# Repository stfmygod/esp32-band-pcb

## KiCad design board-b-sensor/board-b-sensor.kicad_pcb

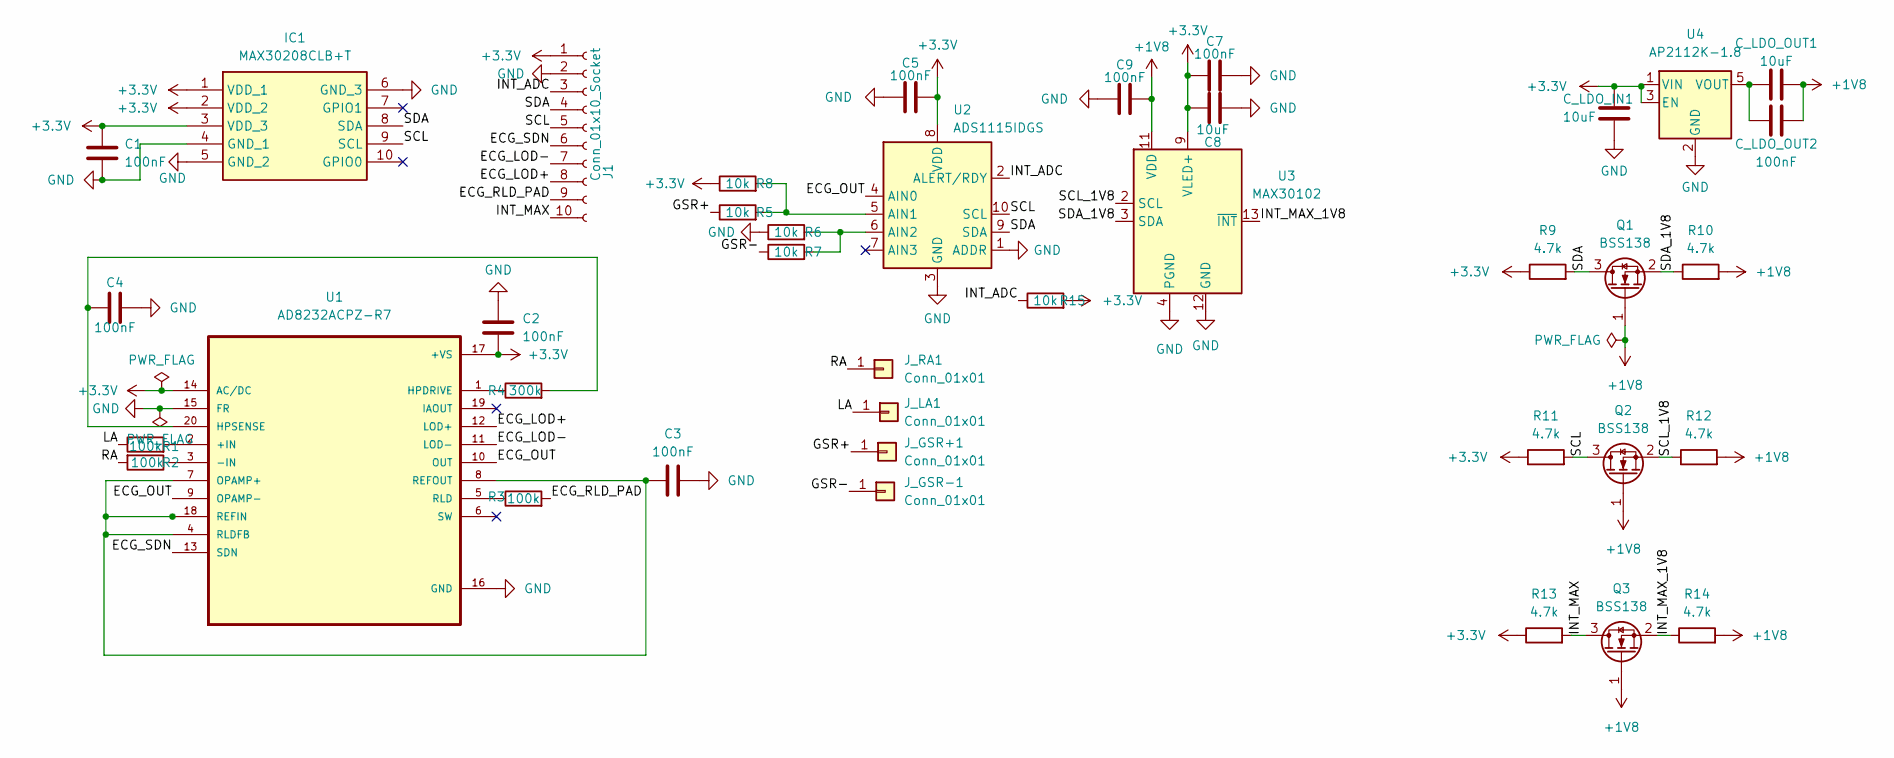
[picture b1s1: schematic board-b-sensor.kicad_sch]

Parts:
C1, C2, C3, C4, C5, C7, C9: 100nF; C_0402_1005Metric
C8: 10uF; C_0805_2012Metric
C_LDO_IN1: 10uF; C_0805_2012Metric
C_LDO_OUT1: 10uF; C_0805_2012Metric
C_LDO_OUT2: 100nF; C_0402_1005Metric
IC1: MAX30208CLB+T; MAX30208CLBT; Manufacturer_Part_Number MAX30208CLB+T; Mouser Part Number 700-MAX30208CLB+T
J1: Conn_01x10_Socket; FPC-SMD_10P-P0.50_XUNPU_FPC-05F-10PH15
J_GSR+1: Conn_01x01; TestPoint_Pad_D2.0mm
J_GSR-1: Conn_01x01; TestPoint_Pad_D2.0mm
J_LA1: Conn_01x01; TestPoint_Pad_D2.0mm
J_RA1: Conn_01x01; TestPoint_Pad_D2.0mm
Q1, Q2, Q3: BSS138; SOT-23
R1, R2, R3: 100k; R_0402_1005Metric
R4: 300k; R_0402_1005Metric
R5, R6, R7, R8, R15: 10k; R_0402_1005Metric
R9, R10, R11, R12, R13, R14: 4.7k; R_0402_1005Metric
U1: AD8232ACPZ-R7; QFN-20-1EP_4x4mm_P0.5mm_EP2.6x2.6mm
U2: ADS1115IDGS; TSSOP-10_3x3mm_P0.5mm
U3: MAX30102; Maxim_OLGA-14_3.3x5.6mm_P0.8mm
U4: AP2112K-1.8; SOT-23-5

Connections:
+1V8: C9.2, C_LDO_OUT1.2, C_LDO_OUT2.1, Q1.1 (G), Q2.1 (G), Q3.1 (G), R10.2, R12.2, R14.2, U3.11 (VDD)
+3.3V: C1.1, C2.2, C5.2, C7.1, C8.1, C_LDO_IN1.2, IC1.1 (VDD_1), IC1.2 (VDD_2), IC1.3 (VDD_3), J1.1, R8.1, R9.1, R11.1, R13.1, R15.2, U1.14 (AC/DC), U1.17 (+VS), U2.8 (VDD), U3.9 (VLED+), U3.10 (VLED+), U4.1 (VIN), U4.3 (EN)
/ECG_LOD+: J1.8, U1.12 (LOD+)
/ECG_LOD-: J1.7, U1.11 (LOD-)
/ECG_OUT: U1.9 (OPAMP-), U1.10 (OUT), U2.4 (AIN0)
/ECG_RLD_PAD: J1.9, R3.2
/ECG_SDN: J1.6, U1.13 (SDN)
/GSR+: J_GSR+1.1 (Pin_1_1), R5.1
/GSR-: J_GSR-1.1 (Pin_1_1), R7.1
/INT_ADC: J1.3, R15.1, U2.2 (ALERT/RDY)
/INT_MAX: J1.10, Q3.3 (D), R13.2
/INT_MAX_1V8: Q3.2 (S), R14.1, U3.13 (~INT)
/LA: J_LA1.1 (Pin_1_1), R1.1
/RA: J_RA1.1 (Pin_1_1), R2.2
/SCL: IC1.9 (SCL), J1.5, Q2.3 (D), R11.2, U2.10 (SCL)
/SCL_1V8: Q2.2 (S), R12.1, U3.2 (SCL)
/SDA: IC1.8 (SDA), J1.4, Q1.3 (D), R9.2, U2.9 (SDA)
/SDA_1V8: Q1.2 (S), R10.1, U3.3 (SDA)
GND: C1.2, C2.1, C3.2, C4.1, C5.1, C7.2, C8.2, C9.1, C_LDO_IN1.1, IC1.4 (GND_1), IC1.5 (GND_2), IC1.6 (GND_3), J1.2, R6.1, U1.15 (FR), U1.16 (GND), U2.1 (ADDR), U2.3 (GND), U3.4 (PGND), U3.12 (GND), U4.2 (GND)
unnamed: R1.2, U1.2 (+IN)
unnamed: R2.1, U1.3 (-IN)
unnamed: R4.1, U1.1 (HPDRIVE)
unnamed: C4.2, R4.2, U1.20 (HPSENSE)
unnamed: C3.1, U1.4 (RLDFB), U1.7 (OPAMP+), U1.8 (REFOUT), U1.18 (REFIN)
unnamed: R3.1, U1.5 (RLD)
unnamed: R5.2, R8.2, U2.5 (AIN1)
unnamed: R6.2, R7.2, U2.6 (AIN2)
unnamed: C_LDO_OUT1.1, C_LDO_OUT2.2, U4.5 (VOUT)

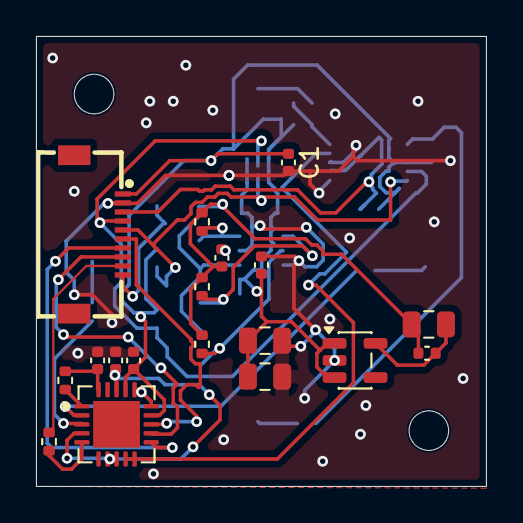
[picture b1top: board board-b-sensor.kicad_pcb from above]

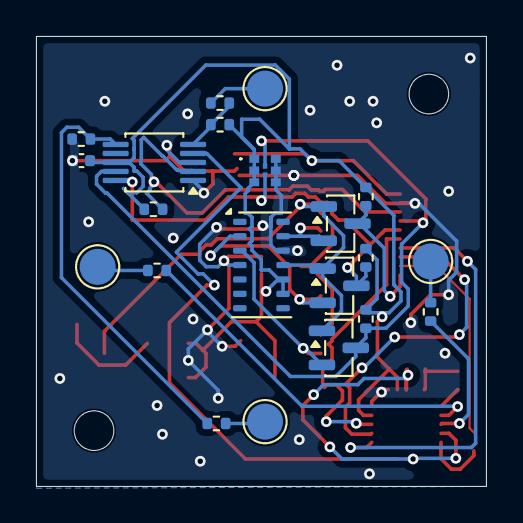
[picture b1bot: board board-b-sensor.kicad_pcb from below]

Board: 2 copper layers, 25.0 x 25.0 mm, 41 parts (21 on the bottom side), 28 nets.

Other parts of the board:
MountingHole1, MountingHole2: MountingHole_2.2mm_M2

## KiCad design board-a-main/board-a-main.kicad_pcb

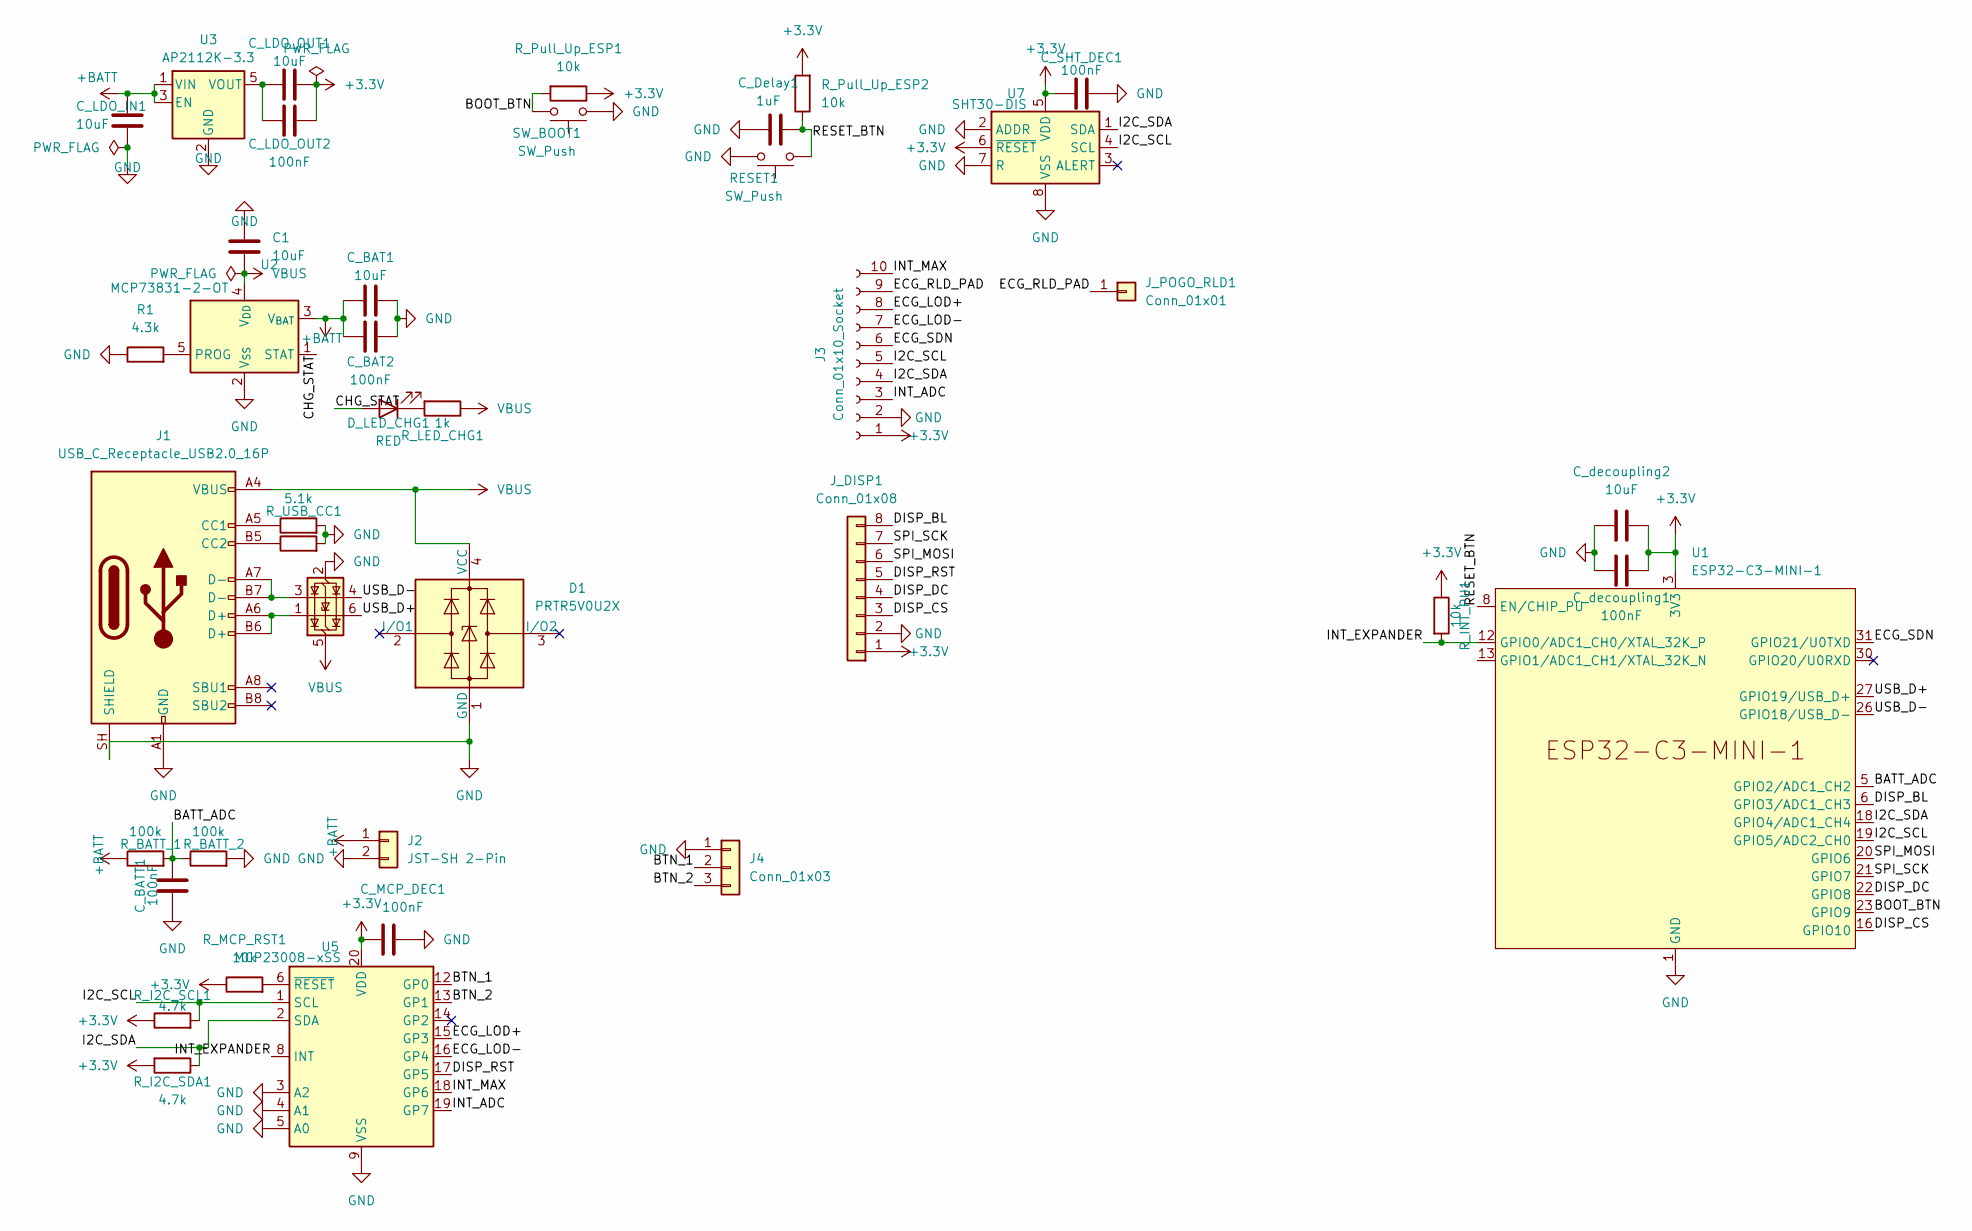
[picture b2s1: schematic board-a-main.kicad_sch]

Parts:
C1: 10uF; C_0805_2012Metric
C_BAT1: 10uF; C_0805_2012Metric
C_BAT2: 100nF; C_0402_1005Metric
C_BATT1: 100nF; C_0402_1005Metric
C_Delay1: 1uF; C_0805_2012Metric
C_LDO_IN1: 10uF; C_0805_2012Metric
C_LDO_OUT1: 10uF; C_0805_2012Metric
C_LDO_OUT2: 100nF; C_0402_1005Metric
C_MCP_DEC1: 100nF; C_0402_1005Metric
C_SHT_DEC1: 100nF; C_0402_1005Metric
C_decoupling1: 100nF; C_0402_1005Metric
C_decoupling2: 10uF; C_0805_2012Metric
D1: PRTR5V0U2X; SOT-143
D_LED_CHG1: RED; LED_0402_1005Metric
J1: USB_C_Receptacle_USB2.0_16P; USB_C_Receptacle_GCT_USB4105-xx-A_16P_TopMnt_Horizontal
J2: JST-SH 2-Pin; JST_SH_SM02B-SRSS-TB_1x02-1MP_P1.00mm_Horizontal
J3: Conn_01x10_Socket; FPC-SMD_10P-P0.50_XUNPU_FPC-05F-10PH15
J4: Conn_01x03; SolderWire-0.127sqmm_1x03_P3.7mm_D0.48mm_OD1mm
J_DISP1: Conn_01x08; Hirose_FH12-8S-0.5SH_1x08-1MP_P0.50mm_Horizontal
J_POGO_RLD1: Conn_01x01; TestPoint_Pad_D2.0mm
R1: 4.3k; R_0402_1005Metric
RESET1: SW_Push; SW_Push_1P1T_NO_CK_KMR2
R_BATT_1, R_BATT_2: 100k; R_0402_1005Metric
R_I2C_SCL1, R_I2C_SDA1: 4.7k; R_0402_1005Metric
R_INT_PU1: 10k; R_0402_1005Metric
R_LED_CHG1: 1k; R_0402_1005Metric
R_MCP_RST1: 10k; R_0402_1005Metric
R_Pull_Up_ESP1, R_Pull_Up_ESP2: 10k; R_0805_2012Metric
R_USB_CC1, R_USB_CC2: 5.1k; R_0402_1005Metric
SW_BOOT1: SW_Push; SW_Push_1P1T_NO_CK_KMR2
U1: ESP32-C3-MINI-1
U2: MCP73831-2-OT; SOT-23-5
U3: AP2112K-3.3; SOT-23-5
U4: USBLC6-2SC6; SOT-23-6
U5: MCP23008-xSS; SSOP-20_5.3x7.2mm_P0.65mm
U7: SHT30-DIS; Sensirion_DFN-8-1EP_2.5x2.5mm_P0.5mm_EP1.1x1.7mm

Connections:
+3.3V: C_LDO_OUT1.2, C_LDO_OUT2.1, C_MCP_DEC1.1, C_SHT_DEC1.2, C_decoupling1.1, C_decoupling2.1, J3.1, J_DISP1.1, R_I2C_SCL1.1, R_I2C_SDA1.2, R_INT_PU1.1, R_MCP_RST1.1, R_Pull_Up_ESP1.1, R_Pull_Up_ESP2.2, U1.3 (3V3), U5.20 (VDD), U7.5 (VDD), U7.6 (~RESET); also elsewhere on the board
+BATT: C_BAT1.1, C_BAT2.1, C_LDO_IN1.2, J2.1, R_BATT_1.1, U2.3 (V_{BAT}), U3.1 (VIN), U3.3 (EN)
/BATT_ADC: C_BATT1.1, R_BATT_1.2, R_BATT_2.1, U1.5 (GPIO2/ADC1_CH2)
/BOOT_BTN: R_Pull_Up_ESP1.2, SW_BOOT1.2, U1.23 (GPIO9); also elsewhere on the board
/BTN_1: J4.2, U5.12 (GP0)
/BTN_2: J4.3, U5.13 (GP1)
/CHG_STAT: D_LED_CHG1.2 (A), U2.1 (STAT)
/DISP_BL: J_DISP1.8, U1.6 (GPIO3/ADC1_CH3)
/DISP_CS: J_DISP1.3, U1.16 (GPIO10)
/DISP_DC: J_DISP1.4, U1.22 (GPIO8)
/DISP_RST: J_DISP1.5, U5.17 (GP5)
/ECG_LOD+: J3.8, U5.15 (GP3)
/ECG_LOD-: J3.7, U5.16 (GP4)
/ECG_RLD_PAD: J3.9, J_POGO_RLD1.1 (Pin_1_1)
/ECG_SDN: J3.6, U1.31 (GPIO21/U0TXD)
/I2C_SCL: J3.5, R_I2C_SCL1.2, U1.19 (GPIO5/ADC2_CH0), U5.1 (SCL), U7.4 (SCL)
/I2C_SDA: J3.4, R_I2C_SDA1.1, U1.18 (GPIO4/ADC1_CH4), U5.2 (SDA), U7.1 (SDA)
/INT_ADC: J3.3, U5.19 (GP7)
/INT_EXPANDER: R_INT_PU1.2, U1.12 (GPIO0/ADC1_CH0/XTAL_32K_P), U5.8 (INT)
/INT_MAX: J3.10, U5.18 (GP6)
/RESET_BTN: C_Delay1.1, RESET1.1, R_Pull_Up_ESP2.1, U1.8 (EN/CHIP_PU)
/SPI_MOSI: J_DISP1.6, U1.20 (GPIO6)
/SPI_SCK: J_DISP1.7, U1.21 (GPIO7)
/USB_D+: U1.27 (GPIO19/USB_D+), U4.6 (I/O1)
/USB_D-: U1.26 (GPIO18/USB_D-), U4.4 (I/O2)
GND: C1.1, C_BAT1.2, C_BAT2.2, C_BATT1.2, C_Delay1.2, C_LDO_IN1.1, C_MCP_DEC1.2, C_SHT_DEC1.1, C_decoupling1.2, C_decoupling2.2, D1.1 (GND), J1.A1 (GND), J1.A12 (GND), J1.B1 (GND), J1.B12 (GND), J1.SH (SHIELD), J2.2, J3.2, J4.1, J_DISP1.2, R1.1, RESET1.2, R_BATT_2.2, R_USB_CC1.2, R_USB_CC2.2, SW_BOOT1.1, U1.1 (GND), U1.2 (GND), U1.11 (GND), U1.14 (GND), U1.36 (GND), U1.37 (GND), U1.38 (GND), U1.39 (GND), U1.40 (GND), U1.41 (GND), U1.42 (GND), U1.43 (GND), U1.44 (GND), U1.45 (GND), U1.46 (GND), U1.47 (GND), U1.48 (GND), U1.49 (GND), U1.50 (GND), U1.51 (GND), U1.52 (GND), U1.53 (GND), U2.2 (V_{SS}), U3.2 (GND), U4.2 (GND), U5.3 (A2), U5.4 (A1), U5.5 (A0), U5.9 (VSS), U7.2 (ADDR), U7.7 (R), U7.8 (VSS), U7.9 (VSS); also elsewhere on the board
unnamed: D_LED_CHG1.1 (K), R_LED_CHG1.2
unnamed: J1.A5 (CC1), R_USB_CC1.1
unnamed: J1.B5 (CC2), R_USB_CC2.1
unnamed: J1.A6 (D+), J1.B6 (D+), U4.1 (I/O1)
unnamed: J1.A7 (D-), J1.B7 (D-), U4.3 (I/O2)
unnamed: R1.2, U2.5 (PROG)
unnamed: C_LDO_OUT1.1, C_LDO_OUT2.2, U3.5 (VOUT)
unnamed: R_MCP_RST1.2, U5.6 (~RESET)
VBUS: C1.2, D1.4 (VCC), J1.A4 (VBUS), J1.A9 (VBUS), J1.B4 (VBUS), J1.B9 (VBUS), R_LED_CHG1.1, U2.4 (V_{DD}), U4.5 (VBUS)

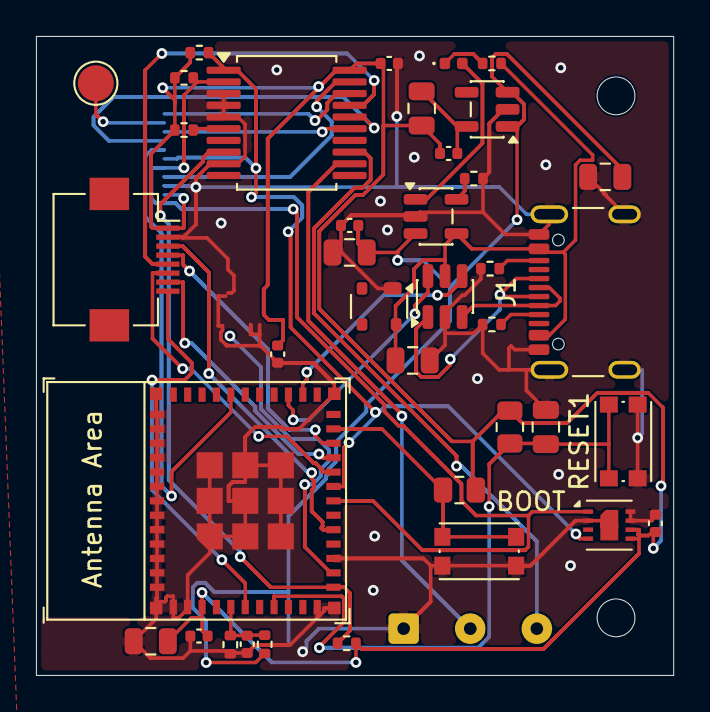
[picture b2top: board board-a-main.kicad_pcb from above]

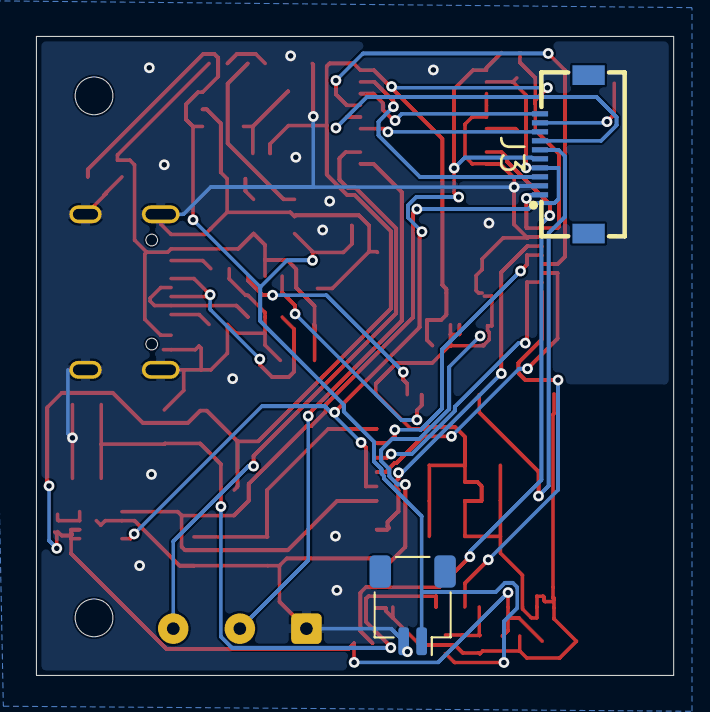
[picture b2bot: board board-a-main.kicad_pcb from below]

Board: 2 copper layers, 35.4 x 35.5 mm, 43 parts (2 on the bottom side), 35 nets.

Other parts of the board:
BOOT: SW_Push; SW_Push_1P1T_NO_CK_KMR2
C_IMU_DEC1: 100nF; C_0402_1005Metric
REF1, REF2: MountingHole_2.1mm

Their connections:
+3.3V: C_IMU_DEC1.1; also elsewhere on the board
/BOOT_BTN: BOOT.2; also elsewhere on the board
GND: BOOT.1, C_IMU_DEC1.2; also elsewhere on the board

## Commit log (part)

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2026-05-29 init: PCB project with .gitignore
2026-05-29 session-0: project setup + library registration
    - Created board-b-sensor and board-a-main KiCAD projects
    - Registered custom footprint library (global)
    - Registered symbol libraries: Espressif, MAX30208, AD8232, BMI160, MAX30102 (global)
    - Created Pogo_P75B1_TH footprint (TH, 1.5mm pad, 1.1mm drill)
    - Snapshot session-0-setup for both projects
2026-05-30 session-1/2: board-b schematic + PCB progress, update gitignore
